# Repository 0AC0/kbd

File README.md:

# Keyboard
 
status: almost unfinished

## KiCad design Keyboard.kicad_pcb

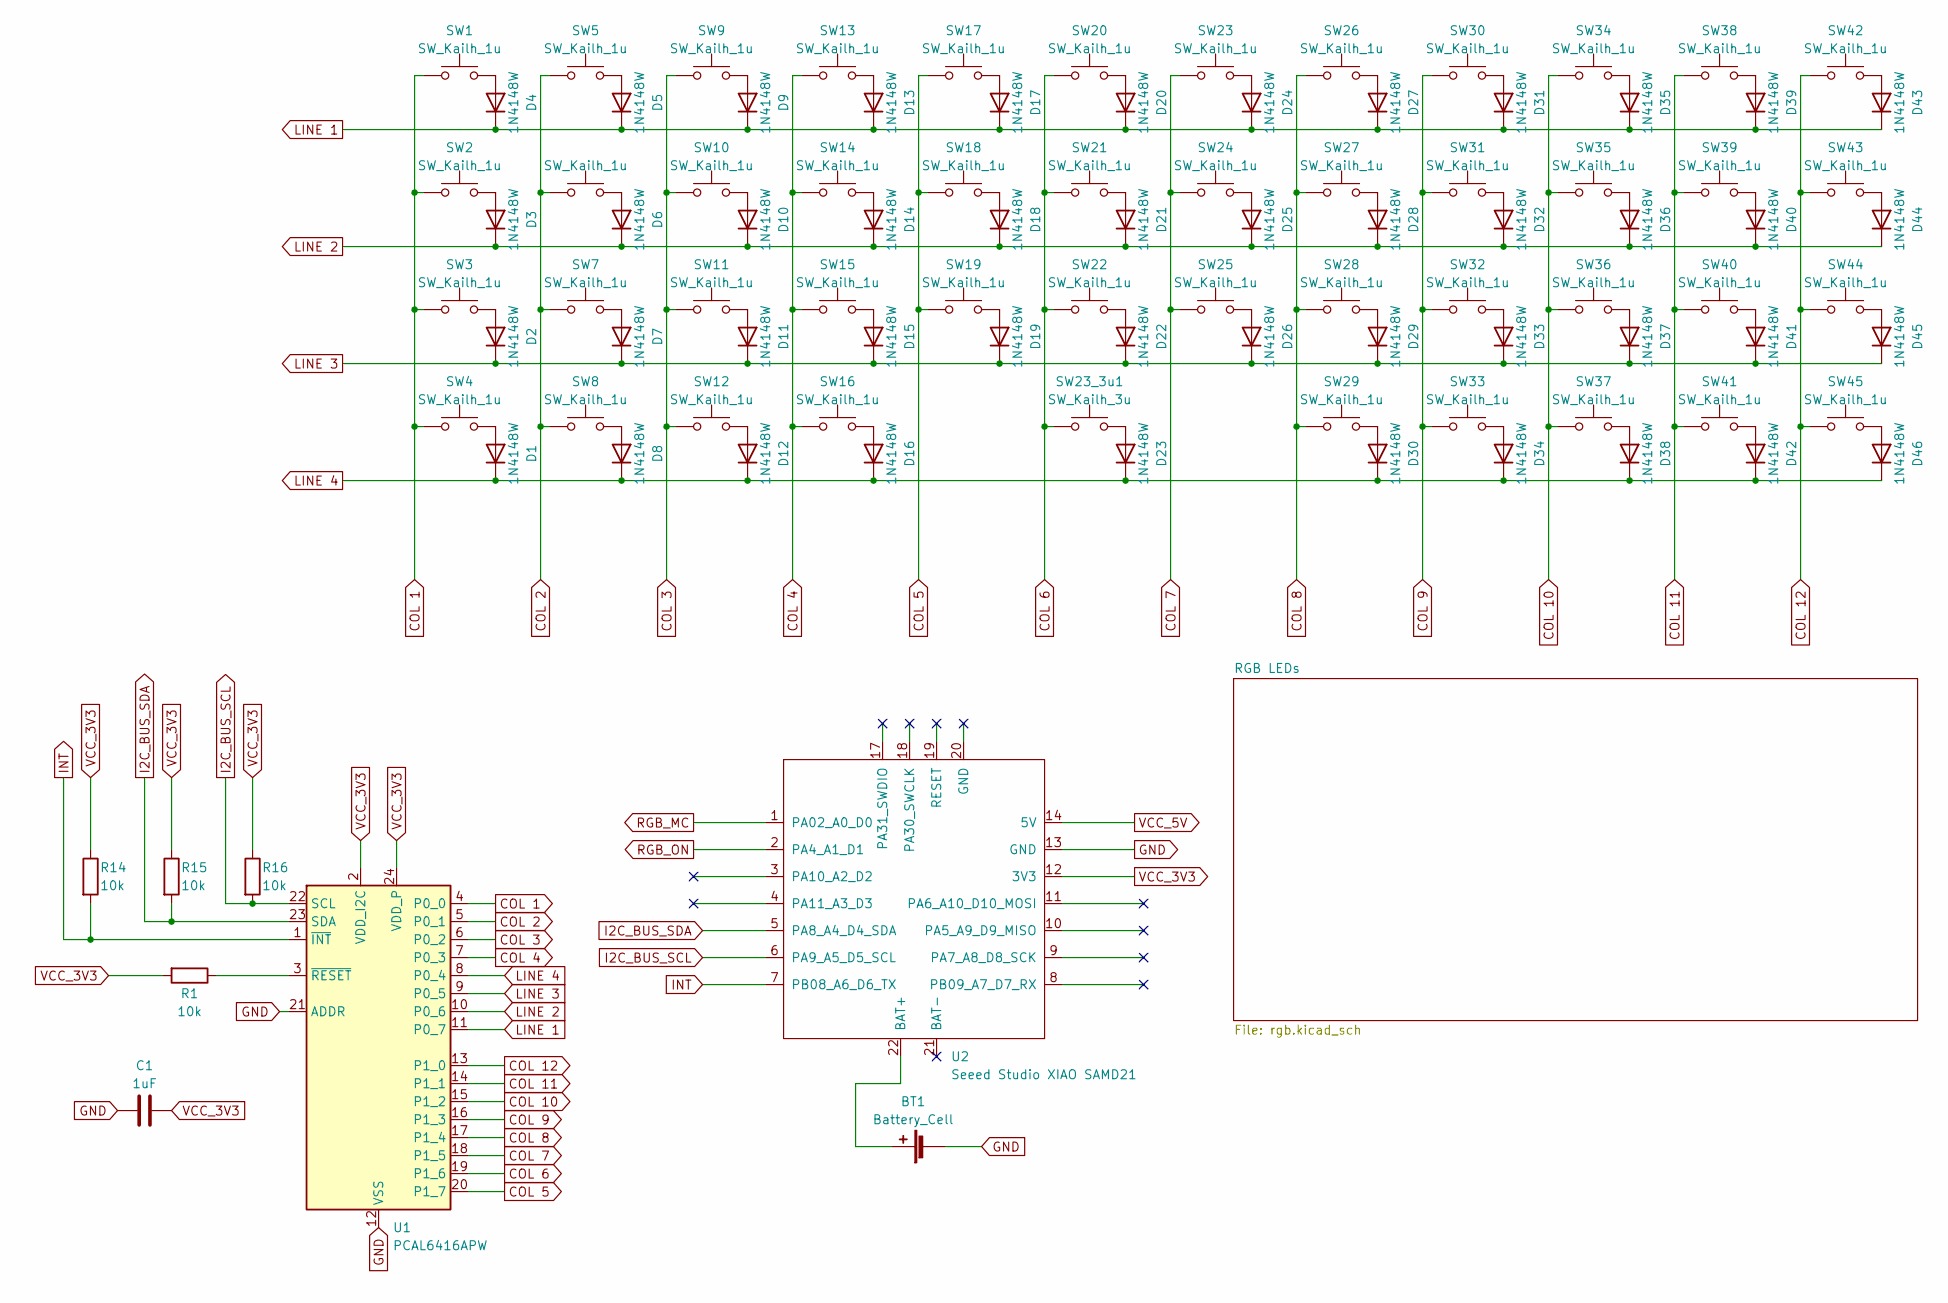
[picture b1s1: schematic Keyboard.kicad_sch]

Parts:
BT1: Battery_Cell; PinHeader_1x02_P2.54mm_Vertical
C1: 1uF; C_0805_2012Metric_Pad1.18x1.45mm_HandSolder
D1, D2, D3, D4, D5, D6, D7, D8, D9, D10, D11, D12, D13, D14, D15, D16, D17, D18, D19, D20, D21, D22, D23, D24, D25, D26, D27, D28, D29, D30, D31, D32, D33, D34, D35, D36, D37, D38, D39, D40, D41, D42, D43, D44, D45, D46: 1N4148W; D_SOD-123
R1, R14, R15, R16: 10k; R_1206_3216Metric_Pad1.30x1.75mm_HandSolder
SW1, SW2, SW3, SW4, SW5, SW6, SW7, SW8, SW9, SW10, SW11, SW12, SW13, SW14, SW15, SW16, SW17, SW18, SW19, SW20, SW21, SW22, SW23, SW24, SW25, SW26, SW27, SW28, SW29, SW30, SW31, SW32, SW33, SW34, SW35, SW36, SW37, SW38, SW39, SW40, SW41, SW42, SW43, SW44, SW45: SW_Kailh_1u; SW_Hotswap_Kailh_Choc_V1V2_1.00u
SW23_3u1: SW_Kailh_3u; SW_Hotswap_Kailh_Choc_V1V2_3.00u
U1: PCAL6416APW; TSSOP-24_4.4x7.8mm_P0.65mm
U2: Seeed Studio XIAO SAMD21; XIAO-nRF52840-Sense-14P-2.54-21X17.8MM

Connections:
COL 1: SW1.1, SW2.1, SW3.1, SW4.1, U1.4 (P0_0)
COL 2: SW5.1, SW6.1, SW7.1, SW8.1, U1.5 (P0_1)
COL 3: SW9.1, SW10.1, SW11.1, SW12.1, U1.6 (P0_2)
COL 4: SW13.1, SW14.1, SW15.1, SW16.1, U1.7 (P0_3)
COL 5: SW17.1, SW18.1, SW19.1, U1.20 (P1_7)
COL 6: SW20.1, SW21.1, SW22.1, SW23_3u1.1, U1.19 (P1_6)
COL 7: SW23.1, SW24.1, SW25.1, U1.18 (P1_5)
COL 8: SW26.1, SW27.1, SW28.1, SW29.1, U1.17 (P1_4)
COL 9: SW30.1, SW31.1, SW32.1, SW33.1, U1.16 (P1_3)
COL 10: SW34.1, SW35.1, SW36.1, SW37.1, U1.15 (P1_2)
COL 11: SW38.1, SW39.1, SW40.1, SW41.1, U1.14 (P1_1)
COL 12: SW42.1, SW43.1, SW44.1, SW45.1, U1.13 (P1_0)
GND: BT1.2 (-), C1.2, U1.12 (VSS), U1.21 (ADDR), U2.13 (GND); also elsewhere on the board
I2C_BUS_SCL: R16.2, U1.22 (SCL), U2.6 (PA9_A5_D5_SCL)
I2C_BUS_SDA: R15.2, U1.23 (SDA), U2.5 (PA8_A4_D4_SDA)
INT: R14.2, U1.1 (~INT), U2.7 (PB08_A6_D6_TX)
LINE 1: D4.1 (K), D5.1 (K), D9.1 (K), D13.1 (K), D17.1 (K), D20.1 (K), D24.1 (K), D27.1 (K), D31.1 (K), D35.1 (K), D39.1 (K), D43.1 (K), U1.11 (P0_7)
LINE 2: D3.1 (K), D6.1 (K), D10.1 (K), D14.1 (K), D18.1 (K), D21.1 (K), D25.1 (K), D28.1 (K), D32.1 (K), D36.1 (K), D40.1 (K), D44.1 (K), U1.10 (P0_6)
LINE 3: D2.1 (K), D7.1 (K), D11.1 (K), D15.1 (K), D19.1 (K), D22.1 (K), D26.1 (K), D29.1 (K), D33.1 (K), D37.1 (K), D41.1 (K), D45.1 (K), U1.9 (P0_5)
LINE 4: D1.1 (K), D8.1 (K), D12.1 (K), D16.1 (K), D23.1 (K), D30.1 (K), D34.1 (K), D38.1 (K), D42.1 (K), D46.1 (K), U1.8 (P0_4)
unnamed: BT1.1 (+), U2.22 (BAT+)
unnamed: D1.2 (A), SW4.2
unnamed: D2.2 (A), SW3.2
unnamed: D3.2 (A), SW2.2
unnamed: D4.2 (A), SW1.2
unnamed: D5.2 (A), SW5.2
unnamed: D6.2 (A), SW6.2
unnamed: D7.2 (A), SW7.2
unnamed: D8.2 (A), SW8.2
unnamed: D9.2 (A), SW9.2
unnamed: D10.2 (A), SW10.2
unnamed: D11.2 (A), SW11.2
unnamed: D12.2 (A), SW12.2
unnamed: D13.2 (A), SW13.2
unnamed: D14.2 (A), SW14.2
unnamed: D15.2 (A), SW15.2
unnamed: D16.2 (A), SW16.2
unnamed: D17.2 (A), SW17.2
unnamed: D18.2 (A), SW18.2
unnamed: D19.2 (A), SW19.2
unnamed: D20.2 (A), SW20.2
unnamed: D21.2 (A), SW21.2
unnamed: D22.2 (A), SW22.2
unnamed: D23.2 (A), SW23_3u1.2
unnamed: D24.2 (A), SW23.2
unnamed: D25.2 (A), SW24.2
unnamed: D26.2 (A), SW25.2
unnamed: D27.2 (A), SW26.2
unnamed: D28.2 (A), SW27.2
unnamed: D29.2 (A), SW28.2
unnamed: D30.2 (A), SW29.2
unnamed: D31.2 (A), SW30.2
unnamed: D32.2 (A), SW31.2
unnamed: D33.2 (A), SW32.2
unnamed: D34.2 (A), SW33.2
unnamed: D35.2 (A), SW34.2
unnamed: D36.2 (A), SW35.2
unnamed: D37.2 (A), SW36.2
unnamed: D38.2 (A), SW37.2
unnamed: D39.2 (A), SW38.2
unnamed: D40.2 (A), SW39.2
unnamed: D41.2 (A), SW40.2
unnamed: D42.2 (A), SW41.2
unnamed: D43.2 (A), SW42.2
unnamed: D44.2 (A), SW43.2
unnamed: D45.2 (A), SW44.2
unnamed: D46.2 (A), SW45.2
unnamed: R1.1, U1.3 (~RESET)
RGB_MC: U2.1 (PA02_A0_D0); also elsewhere on the board
RGB_ON: U2.2 (PA4_A1_D1); also elsewhere on the board
VCC_3V3: C1.1, R1.2, R14.1, R15.1, R16.1, U1.2 (VDD_I2C), U1.24 (VDD_P), U2.12 (3V3)
VCC_5V: U2.14 (5V); also elsewhere on the board

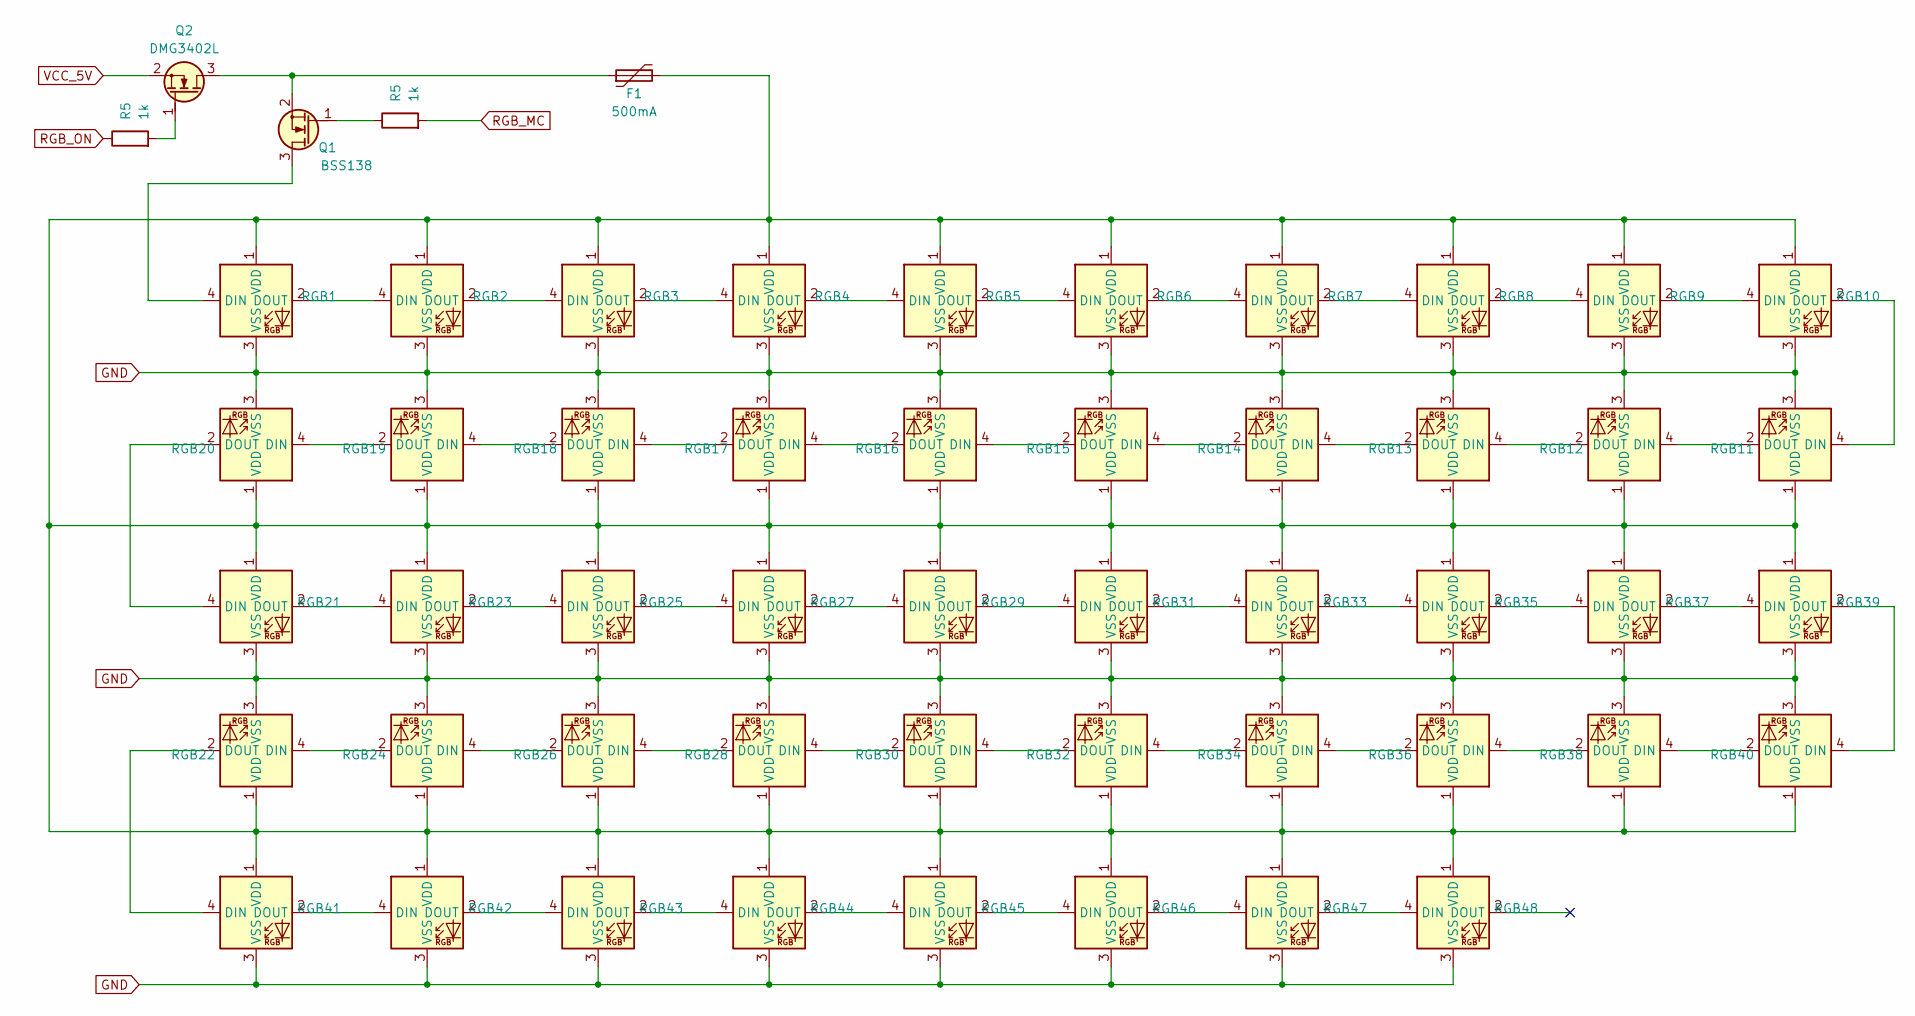
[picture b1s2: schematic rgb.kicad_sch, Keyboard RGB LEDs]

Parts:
F1: 500mA; Fuse_1206_3216Metric_Pad1.42x1.75mm_HandSolder
Q1: BSS138; SOT-23
Q2: DMG3402L; SOT-23
R5: 1k; R_1206_3216Metric_Pad1.30x1.75mm_HandSolder
RGB1, RGB2, RGB3, RGB4, RGB5, RGB6, RGB7, RGB8, RGB9, RGB10, RGB11, RGB12, RGB13, RGB14, RGB15, RGB16, RGB17, RGB18, RGB19, RGB20, RGB21, RGB22, RGB23, RGB24, RGB25, RGB26, RGB27, RGB28, RGB29, RGB30, RGB31, RGB32, RGB33, RGB34, RGB35, RGB36, RGB37, RGB38, RGB39, RGB40, RGB41, RGB42, RGB43, RGB44, RGB45, RGB46, RGB47, RGB48: SK6812-MINI-E

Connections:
GND: RGB1.3 (VSS), RGB2.3 (VSS), RGB3.3 (VSS), RGB4.3 (VSS), RGB5.3 (VSS), RGB6.3 (VSS), RGB7.3 (VSS), RGB8.3 (VSS), RGB9.3 (VSS), RGB10.3 (VSS), RGB11.3 (VSS), RGB12.3 (VSS), RGB13.3 (VSS), RGB14.3 (VSS), RGB15.3 (VSS), RGB16.3 (VSS), RGB17.3 (VSS), RGB18.3 (VSS), RGB19.3 (VSS), RGB20.3 (VSS), RGB21.3 (VSS), RGB22.3 (VSS), RGB23.3 (VSS), RGB24.3 (VSS), RGB25.3 (VSS), RGB26.3 (VSS), RGB27.3 (VSS), RGB28.3 (VSS), RGB29.3 (VSS), RGB30.3 (VSS), RGB31.3 (VSS), RGB32.3 (VSS), RGB33.3 (VSS), RGB34.3 (VSS), RGB35.3 (VSS), RGB36.3 (VSS), RGB37.3 (VSS), RGB38.3 (VSS), RGB39.3 (VSS), RGB40.3 (VSS), RGB41.3 (VSS), RGB42.3 (VSS), RGB43.3 (VSS), RGB44.3 (VSS), RGB45.3 (VSS), RGB46.3 (VSS), RGB47.3 (VSS), RGB48.3 (VSS); also elsewhere on the board
unnamed: Q1.3 (D), RGB1.4 (DIN)
unnamed 68: Q1.1 (G); also elsewhere on the board
unnamed: F1.1, Q1.2 (S), Q2.3 (D)
unnamed 70: Q2.1 (G); also elsewhere on the board
unnamed: RGB1.2 (DOUT), RGB2.4 (DIN)
unnamed: F1.2, RGB1.1 (VDD), RGB2.1 (VDD), RGB3.1 (VDD), RGB4.1 (VDD), RGB5.1 (VDD), RGB6.1 (VDD), RGB7.1 (VDD), RGB8.1 (VDD), RGB9.1 (VDD), RGB10.1 (VDD), RGB11.1 (VDD), RGB12.1 (VDD), RGB13.1 (VDD), RGB14.1 (VDD), RGB15.1 (VDD), RGB16.1 (VDD), RGB17.1 (VDD), RGB18.1 (VDD), RGB19.1 (VDD), RGB20.1 (VDD), RGB21.1 (VDD), RGB22.1 (VDD), RGB23.1 (VDD), RGB24.1 (VDD), RGB25.1 (VDD), RGB26.1 (VDD), RGB27.1 (VDD), RGB28.1 (VDD), RGB29.1 (VDD), RGB30.1 (VDD), RGB31.1 (VDD), RGB32.1 (VDD), RGB33.1 (VDD), RGB34.1 (VDD), RGB35.1 (VDD), RGB36.1 (VDD), RGB37.1 (VDD), RGB38.1 (VDD), RGB39.1 (VDD), RGB40.1 (VDD), RGB41.1 (VDD), RGB42.1 (VDD), RGB43.1 (VDD), RGB44.1 (VDD), RGB45.1 (VDD), RGB46.1 (VDD), RGB47.1 (VDD), RGB48.1 (VDD)
unnamed: RGB2.2 (DOUT), RGB3.4 (DIN)
unnamed: RGB3.2 (DOUT), RGB4.4 (DIN)
unnamed: RGB4.2 (DOUT), RGB5.4 (DIN)
unnamed: RGB5.2 (DOUT), RGB6.4 (DIN)
unnamed: RGB6.2 (DOUT), RGB7.4 (DIN)
unnamed: RGB7.2 (DOUT), RGB8.4 (DIN)
unnamed: RGB8.2 (DOUT), RGB9.4 (DIN)
unnamed: RGB9.2 (DOUT), RGB10.4 (DIN)
unnamed: RGB10.2 (DOUT), RGB11.4 (DIN)
unnamed: RGB11.2 (DOUT), RGB12.4 (DIN)
unnamed: RGB12.2 (DOUT), RGB13.4 (DIN)
unnamed: RGB13.2 (DOUT), RGB14.4 (DIN)
unnamed: RGB14.2 (DOUT), RGB15.4 (DIN)
unnamed: RGB15.2 (DOUT), RGB16.4 (DIN)
unnamed: RGB16.2 (DOUT), RGB17.4 (DIN)
unnamed: RGB17.2 (DOUT), RGB18.4 (DIN)
unnamed: RGB18.2 (DOUT), RGB19.4 (DIN)
unnamed: RGB19.2 (DOUT), RGB20.4 (DIN)
unnamed: RGB20.2 (DOUT), RGB21.4 (DIN)
unnamed: RGB21.2 (DOUT), RGB23.4 (DIN)
unnamed: RGB22.4 (DIN), RGB24.2 (DOUT)
unnamed: RGB22.2 (DOUT), RGB41.4 (DIN)
unnamed: RGB23.2 (DOUT), RGB25.4 (DIN)
unnamed: RGB24.4 (DIN), RGB26.2 (DOUT)
unnamed: RGB25.2 (DOUT), RGB27.4 (DIN)
unnamed: RGB26.4 (DIN), RGB28.2 (DOUT)
unnamed: RGB27.2 (DOUT), RGB29.4 (DIN)
unnamed: RGB28.4 (DIN), RGB30.2 (DOUT)
unnamed: RGB29.2 (DOUT), RGB31.4 (DIN)
unnamed: RGB30.4 (DIN), RGB32.2 (DOUT)
unnamed: RGB31.2 (DOUT), RGB33.4 (DIN)
unnamed: RGB32.4 (DIN), RGB34.2 (DOUT)
unnamed: RGB33.2 (DOUT), RGB35.4 (DIN)
unnamed: RGB34.4 (DIN), RGB36.2 (DOUT)
unnamed: RGB35.2 (DOUT), RGB37.4 (DIN)
unnamed: RGB36.4 (DIN), RGB38.2 (DOUT)
unnamed: RGB37.2 (DOUT), RGB39.4 (DIN)
unnamed: RGB38.4 (DIN), RGB40.2 (DOUT)
unnamed: RGB39.2 (DOUT), RGB40.4 (DIN)
unnamed: RGB41.2 (DOUT), RGB42.4 (DIN)
unnamed: RGB42.2 (DOUT), RGB43.4 (DIN)
unnamed: RGB43.2 (DOUT), RGB44.4 (DIN)
unnamed: RGB44.2 (DOUT), RGB45.4 (DIN)
unnamed: RGB45.2 (DOUT), RGB46.4 (DIN)
unnamed: RGB46.2 (DOUT), RGB47.4 (DIN)
unnamed: RGB47.2 (DOUT), RGB48.4 (DIN)
VCC_5V: Q2.2 (S); also elsewhere on the board

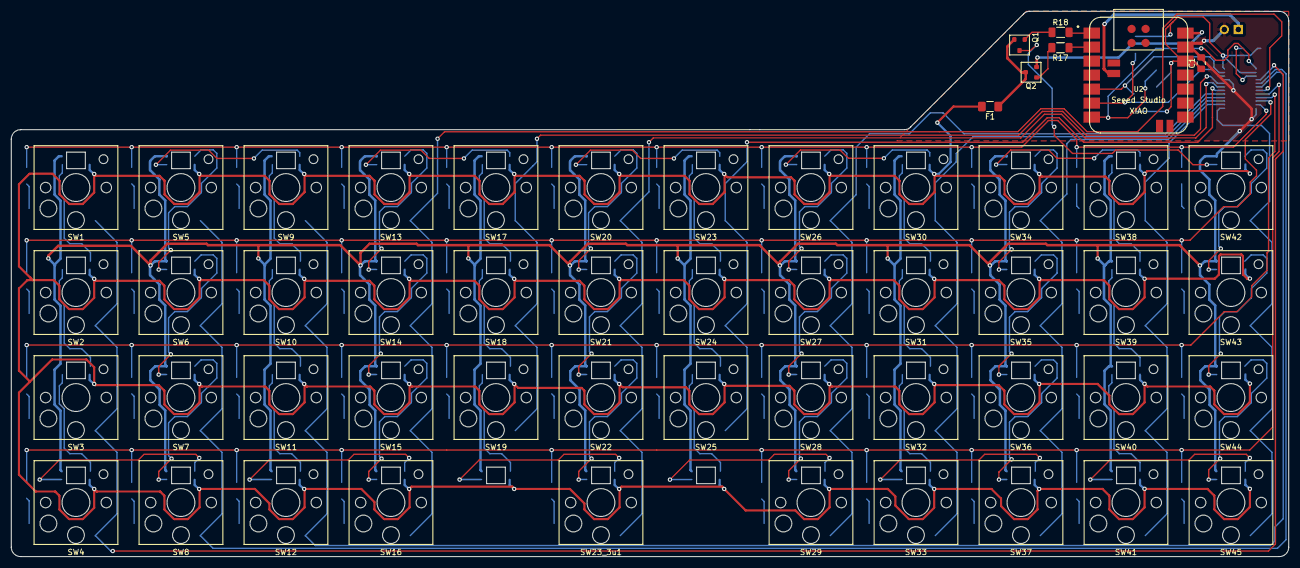
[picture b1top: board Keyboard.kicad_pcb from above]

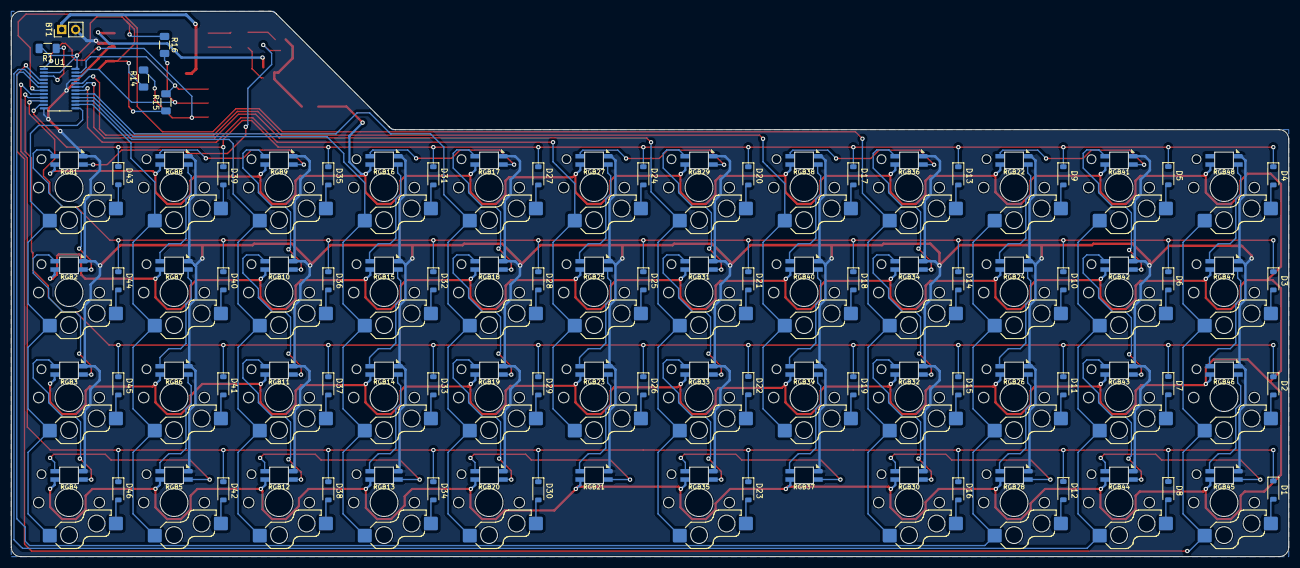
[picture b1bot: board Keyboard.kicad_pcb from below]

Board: 2 copper layers, 231.7 x 98.9 mm, 153 parts (100 on the bottom side), 124 nets.

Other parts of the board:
R17, R18: 1k; R_1206_3216Metric_Pad1.30x1.75mm_HandSolder

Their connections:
unnamed 68: R18.1; also elsewhere on the board
unnamed 70: R17.2; also elsewhere on the board
RGB_MC: R18.2; also elsewhere on the board
RGB_ON: R17.1; also elsewhere on the board

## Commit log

2023-03-11 finished pcb routing
2023-03-11 removed two useless traces
2023-03-13 rev 1.2
2023-03-14 rounded corners, replaced current reg with fuse
2023-03-15 changed led mosfet and resistors
